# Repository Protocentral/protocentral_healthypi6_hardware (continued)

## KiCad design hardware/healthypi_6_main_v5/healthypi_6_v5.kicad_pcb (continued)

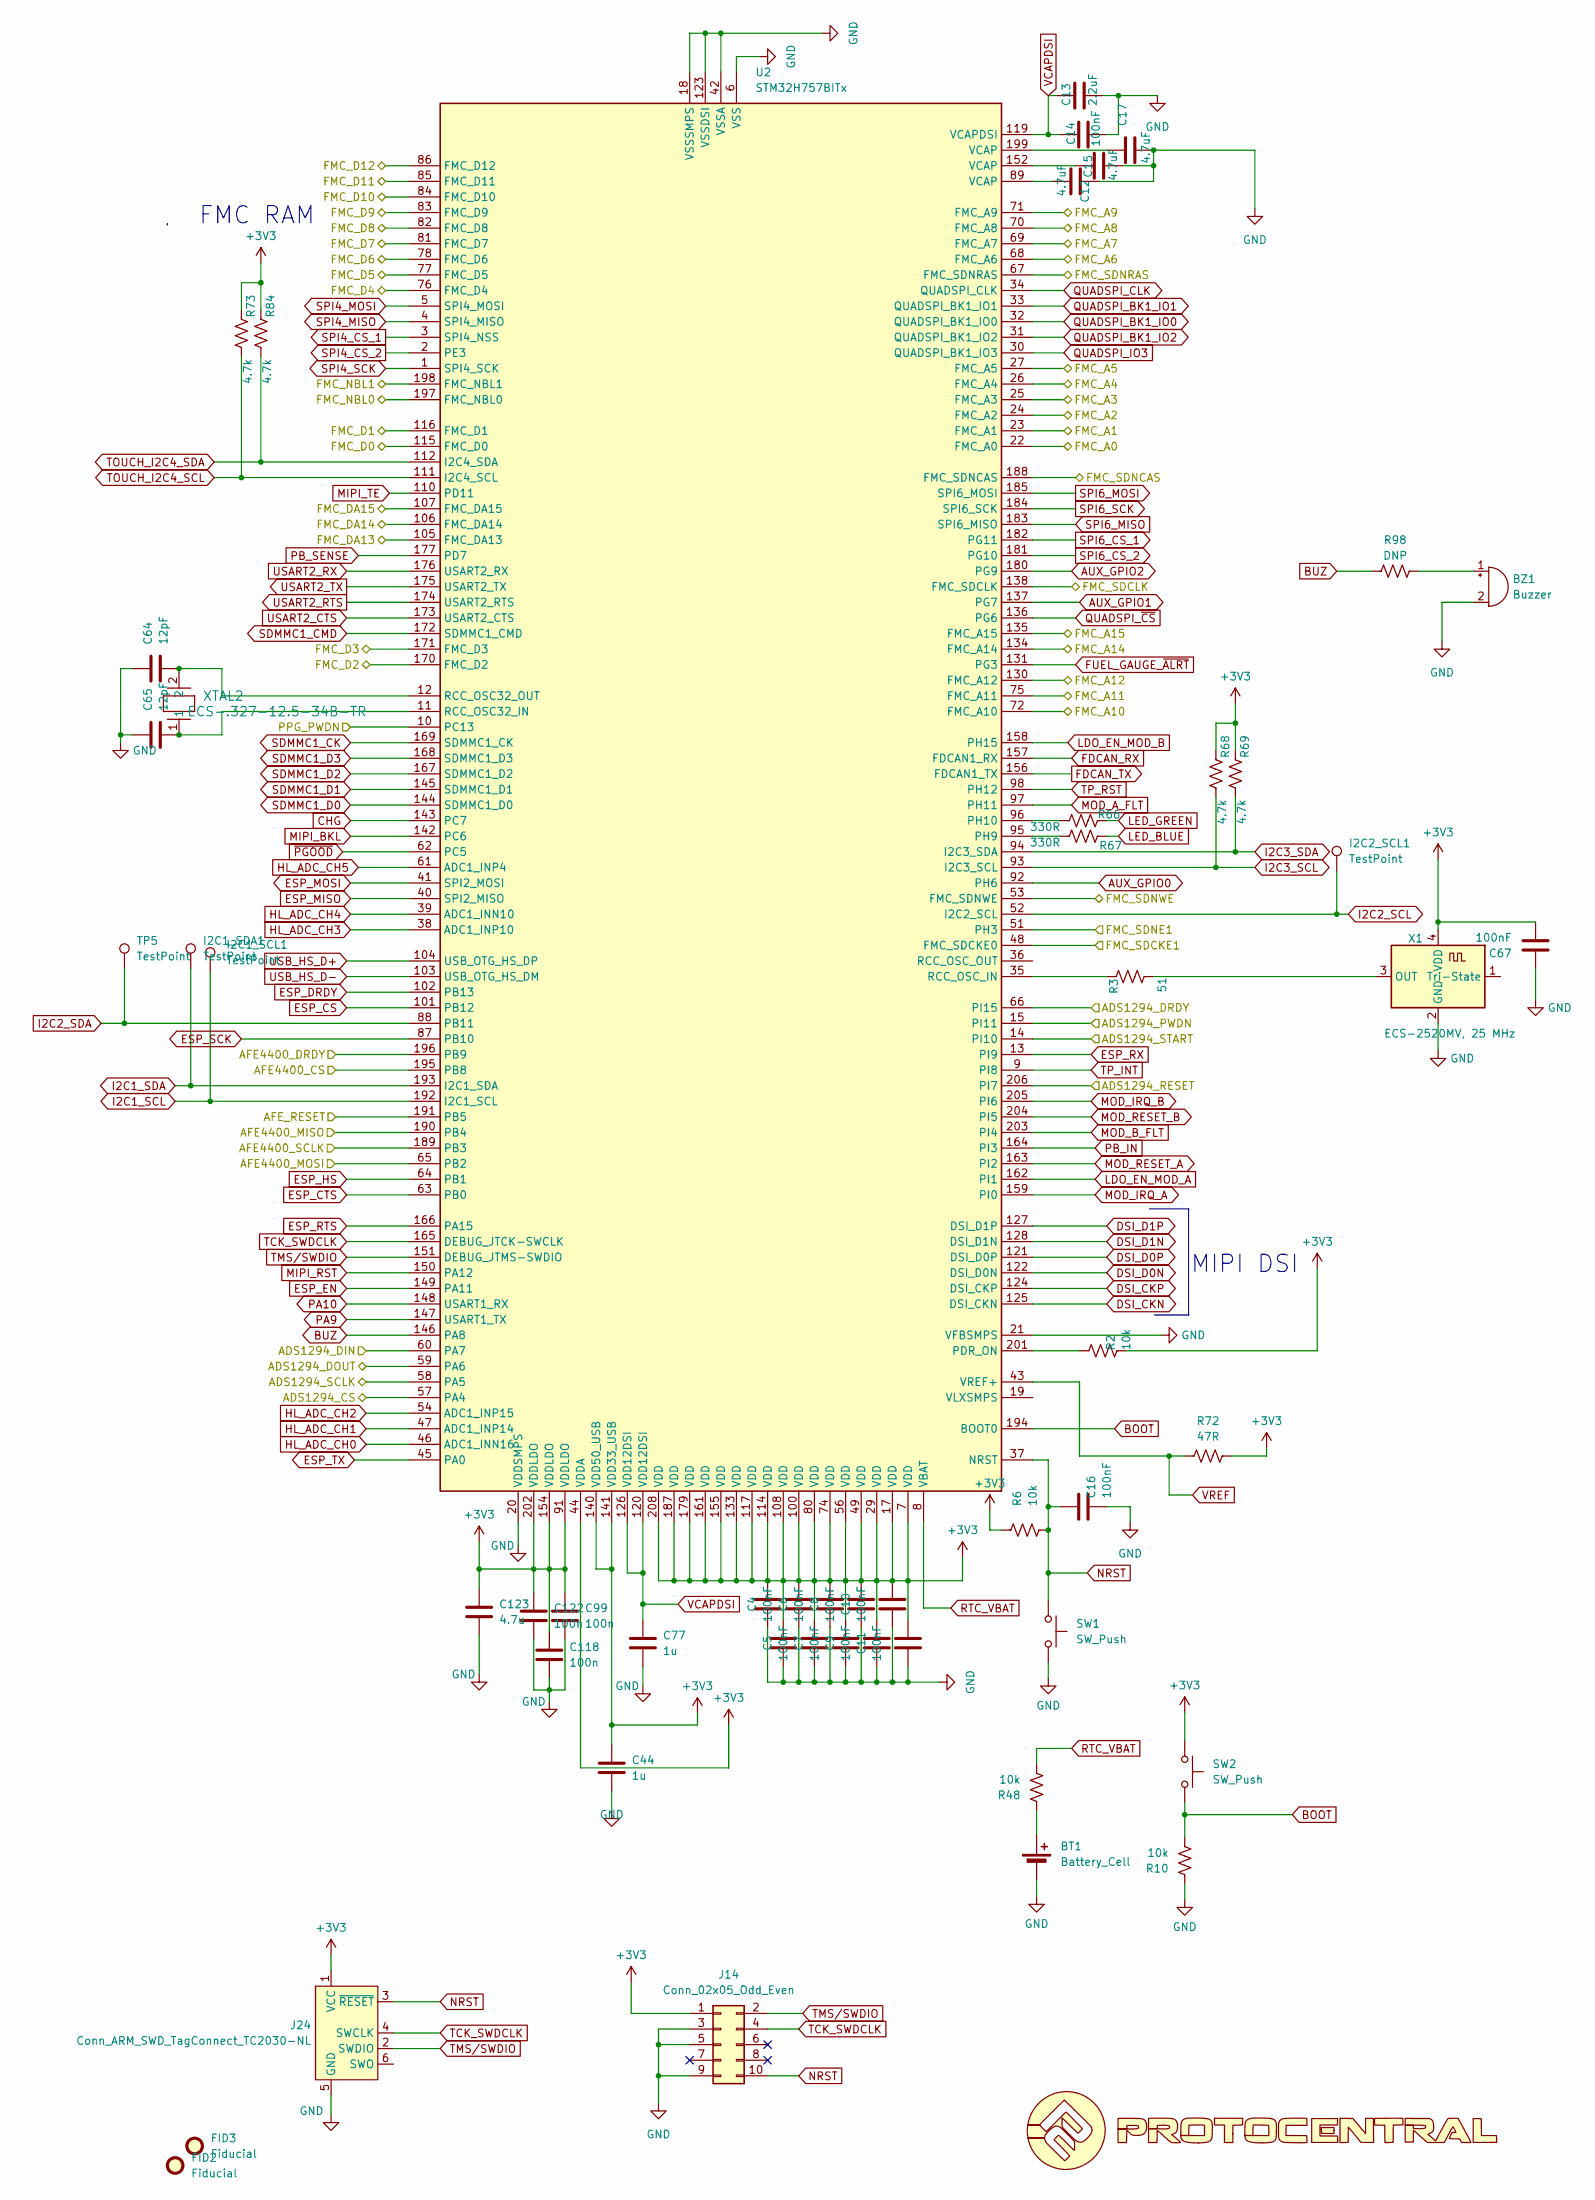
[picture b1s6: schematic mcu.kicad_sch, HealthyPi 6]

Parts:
BT1: Battery_Cell; BatteryHolder_Keystone_3001_1x12mm
BZ1: Buzzer; Buzzer_Murata_PKMCS0909E
C2, C3, C4, C5, C6, C7, C8, C9, C10, C11, C14, C16, C67: 100nF; C_0402_1005Metric
C12, C15, C17: 4.7uF; C_0402_1005Metric
C13: 2.2uF; C_0402_1005Metric
C44, C77: 1u; C_0402_1005Metric
C64, C65: 12pF; C_0402_1005Metric
C99, C118, C122: 100n; C_0402_1005Metric
C123: 4.7u; C_0402_1005Metric
FID2, FID3: Fiducial; Fiducial_1mm_Mask3mm
I2C1_SCL1, I2C1_SDA1, I2C2_SCL1: TestPoint; TestPoint_Pad_D1.0mm
J14: Conn_02x05_Odd_Even; PinHeader_2x05_P1.27mm_Vertical_SMD
J24: Conn_ARM_SWD_TagConnect_TC2030-NL; Tag-Connect_TC2030-IDC-NL_2x03_P1.27mm_Vertical
R2, R6, R10, R48: 10k; R_0402_1005Metric
R3: 51; R_0402_1005Metric
R66, R67: 330R; R_0402_1005Metric
R68, R69, R73, R84: 4.7k; R_0402_1005Metric
R72: 47R; R_0402_1005Metric
R98: DNP; R_0402_1005Metric
SW1, SW2: SW_Push; SW_Push_1P1T_NO_CK_KMR2
TP5: TestPoint; TestPoint_Pad_D1.0mm
U2: STM32H757BITx; LQFP-208_28x28mm_P0.5mm
U10: LOGO
X1: ECS-2520MV, 25 MHz; Oscillator_SMD_ECS_2520MV-xxx-xx-4Pin_2.5x2.0mm
XTAL2: ECS-.327-12.5-34B-TR; XTAL_ECS-31B_ECS

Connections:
+3V3: C2.2, C3.2, C4.2, C5.2, C6.2, C7.2, C8.2, C9.2, C10.2, C11.2, C44.1, C67.2, C99.1, C118.1, C122.1, C123.1, J14.1, J24.1 (VCC), R2.2, R6.1, R68.2, R69.2, R72.1, R73.2, R84.2, SW2.1, U2.7 (VDD), U2.17 (VDD), U2.29 (VDD), U2.44 (VDDA), U2.49 (VDD), U2.56 (VDD), U2.74 (VDD), U2.80 (VDD), U2.91 (VDDLDO), U2.100 (VDD), U2.108 (VDD), U2.114 (VDD), U2.117 (VDD), U2.133 (VDD), U2.140 (VDD50_USB), U2.141 (VDD33_USB), U2.154 (VDDLDO), U2.155 (VDD), U2.161 (VDD), U2.179 (VDD), U2.187 (VDD), U2.202 (VDDLDO), U2.208 (VDD), X1.4 (VDD); also elsewhere on the board
/ECG Frontend/ADS1294_CS: U2.57 (PA4); also elsewhere on the board
/ECG Frontend/ADS1294_DIN: U2.60 (PA7); also elsewhere on the board
/ECG Frontend/ADS1294_DOUT: U2.59 (PA6); also elsewhere on the board
/ECG Frontend/ADS1294_DRDY: U2.66 (PI15); also elsewhere on the board
/ECG Frontend/ADS1294_PWDN: U2.15 (PI11); also elsewhere on the board
/ECG Frontend/ADS1294_RESET: U2.206 (PI7); also elsewhere on the board
/ECG Frontend/ADS1294_SCLK: U2.58 (PA5); also elsewhere on the board
/ECG Frontend/ADS1294_START: U2.14 (PI10); also elsewhere on the board
/MCU/AFE4400_CS: U2.195 (PB8); also elsewhere on the board
/MCU/AFE4400_DRDY: U2.196 (PB9); also elsewhere on the board
/MCU/AFE4400_MISO: U2.190 (PB4); also elsewhere on the board
/MCU/AFE4400_MOSI: U2.65 (PB2); also elsewhere on the board
/MCU/AFE4400_SCLK: U2.189 (PB3); also elsewhere on the board
/MCU/AFE_RESET: U2.191 (PB5); also elsewhere on the board
/MCU/FMC_A0: U2.22 (FMC_A0); also elsewhere on the board
/MCU/FMC_A1: U2.23 (FMC_A1); also elsewhere on the board
/MCU/FMC_A2: U2.24 (FMC_A2); also elsewhere on the board
/MCU/FMC_A3: U2.25 (FMC_A3); also elsewhere on the board
/MCU/FMC_A4: U2.26 (FMC_A4); also elsewhere on the board
/MCU/FMC_A5: U2.27 (FMC_A5); also elsewhere on the board
/MCU/FMC_A6: U2.68 (FMC_A6); also elsewhere on the board
/MCU/FMC_A7: U2.69 (FMC_A7); also elsewhere on the board
/MCU/FMC_A8: U2.70 (FMC_A8); also elsewhere on the board
/MCU/FMC_A9: U2.71 (FMC_A9); also elsewhere on the board
/MCU/FMC_A10: U2.72 (FMC_A10); also elsewhere on the board
/MCU/FMC_A11: U2.75 (FMC_A11); also elsewhere on the board
/MCU/FMC_A12: U2.130 (FMC_A12); also elsewhere on the board
/MCU/FMC_A14: U2.134 (FMC_A14); also elsewhere on the board
/MCU/FMC_A15: U2.135 (FMC_A15); also elsewhere on the board
/MCU/FMC_D0: U2.115 (FMC_D0); also elsewhere on the board
/MCU/FMC_D1: U2.116 (FMC_D1); also elsewhere on the board
/MCU/FMC_D2: U2.170 (FMC_D2); also elsewhere on the board
/MCU/FMC_D3: U2.171 (FMC_D3); also elsewhere on the board
/MCU/FMC_D4: U2.76 (FMC_D4); also elsewhere on the board
/MCU/FMC_D5: U2.77 (FMC_D5); also elsewhere on the board
/MCU/FMC_D6: U2.78 (FMC_D6); also elsewhere on the board
/MCU/FMC_D7: U2.81 (FMC_D7); also elsewhere on the board
/MCU/FMC_D8: U2.82 (FMC_D8); also elsewhere on the board
/MCU/FMC_D9: U2.83 (FMC_D9); also elsewhere on the board
/MCU/FMC_D10: U2.84 (FMC_D10); also elsewhere on the board
/MCU/FMC_D11: U2.85 (FMC_D11); also elsewhere on the board
/MCU/FMC_D12: U2.86 (FMC_D12); also elsewhere on the board
/MCU/FMC_DA13: U2.105 (FMC_DA13); also elsewhere on the board
/MCU/FMC_DA14: U2.106 (FMC_DA14); also elsewhere on the board
/MCU/FMC_DA15: U2.107 (FMC_DA15); also elsewhere on the board
/MCU/FMC_NBL0: U2.197 (FMC_NBL0); also elsewhere on the board
/MCU/FMC_NBL1: U2.198 (FMC_NBL1); also elsewhere on the board
/MCU/FMC_SDCKE1: U2.48 (FMC_SDCKE0); also elsewhere on the board
/MCU/FMC_SDCLK: U2.138 (FMC_SDCLK); also elsewhere on the board
/MCU/FMC_SDNCAS: U2.188 (FMC_SDNCAS); also elsewhere on the board
/MCU/FMC_SDNE1: U2.51 (PH3); also elsewhere on the board
/MCU/FMC_SDNRAS: U2.67 (FMC_SDNRAS); also elsewhere on the board
/MCU/FMC_SDNWE: U2.53 (FMC_SDNWE); also elsewhere on the board
/MCU/PPG_PWDN: U2.10 (PC13); also elsewhere on the board
AUX_GPIO0: U2.92 (PH6); also elsewhere on the board
AUX_GPIO1: U2.137 (PG7); also elsewhere on the board
AUX_GPIO2: U2.180 (PG9); also elsewhere on the board
BOOT: R10.2, SW2.2, U2.194 (BOOT0)
BUZ: R98.1, U2.146 (PA8)
CHG: U2.143 (PC7); also elsewhere on the board
DSI_CKN: U2.125 (DSI_CKN); also elsewhere on the board
DSI_CKP: U2.124 (DSI_CKP); also elsewhere on the board
DSI_D0N: U2.122 (DSI_D0N); also elsewhere on the board
DSI_D0P: U2.121 (DSI_D0P); also elsewhere on the board
DSI_D1N: U2.128 (DSI_D1N); also elsewhere on the board
DSI_D1P: U2.127 (DSI_D1P); also elsewhere on the board
ESP_CS: U2.101 (PB12); also elsewhere on the board
ESP_CTS: U2.63 (PB0); also elsewhere on the board
ESP_DRDY: U2.102 (PB13); also elsewhere on the board
ESP_EN: U2.149 (PA11); also elsewhere on the board
ESP_HS: U2.64 (PB1); also elsewhere on the board
ESP_MISO: U2.40 (SPI2_MISO); also elsewhere on the board
ESP_MOSI: U2.41 (SPI2_MOSI); also elsewhere on the board
ESP_RTS: U2.166 (PA15); also elsewhere on the board
ESP_RX: U2.13 (PI9); also elsewhere on the board
ESP_SCK: U2.87 (PB10); also elsewhere on the board
ESP_TX: U2.45 (PA0); also elsewhere on the board
FDCAN_RX: U2.157 (FDCAN1_RX); also elsewhere on the board
FDCAN_TX: U2.156 (FDCAN1_TX); also elsewhere on the board
FUEL_GAUGE_~ALRT: U2.131 (PG3); also elsewhere on the board
GND: BT1.2 (-), BZ1.2 (-), C2.1, C3.1, C4.1, C5.1, C6.1, C7.1, C8.1, C9.1, C10.1, C11.1, C12.2, C13.2, C14.2, C15.2, C16.2, C17.2, C44.2, C64.1, C65.1, C67.1, C77.2, C99.2, C118.2, C122.2, C123.2, J14.3, J14.5, J14.9, J24.5 (GND), R10.1, SW1.2, U2.6 (VSS), U2.16 (VSS), U2.18 (VSSSMPS), U2.20 (VDDSMPS), U2.21 (VFBSMPS), U2.28 (VSS), U2.42 (VSSA), U2.50 (VSS), U2.55 (VSS), U2.73 (VSS), U2.79 (VSS), U2.90 (VSS), U2.99 (VSS), U2.109 (VSS), U2.113 (VSS), U2.118 (VSS), U2.123 (VSSDSI), U2.129 (VSSDSI), U2.132 (VSS), U2.139 (VSS), U2.153 (VSS), U2.160 (VSS), U2.178 (VSS), U2.186 (VSS), U2.200 (VSS), U2.207 (VSS), X1.2 (GND); also elsewhere on the board
HL_ADC_CH0: U2.46 (ADC1_INN16); also elsewhere on the board
HL_ADC_CH1: U2.47 (ADC1_INP14); also elsewhere on the board
HL_ADC_CH2: U2.54 (ADC1_INP15); also elsewhere on the board
HL_ADC_CH3: U2.38 (ADC1_INP10); also elsewhere on the board
HL_ADC_CH4: U2.39 (ADC1_INN10); also elsewhere on the board
HL_ADC_CH5: U2.61 (ADC1_INP4); also elsewhere on the board
I2C1_SCL: I2C1_SCL1.1 (1_1), U2.192 (I2C1_SCL); also elsewhere on the board
I2C1_SDA: I2C1_SDA1.1 (1_1), U2.193 (I2C1_SDA); also elsewhere on the board
I2C2_SCL: I2C2_SCL1.1 (1_1), U2.52 (I2C2_SCL); also elsewhere on the board
I2C2_SDA: TP5.1 (1_1), U2.88 (PB11); also elsewhere on the board
I2C3_SCL: R68.1, U2.93 (I2C3_SCL); also elsewhere on the board
I2C3_SDA: R69.1, U2.94 (I2C3_SDA); also elsewhere on the board
LDO_EN_MOD_A: U2.162 (PI1); also elsewhere on the board
LDO_EN_MOD_B: U2.158 (PH15); also elsewhere on the board
LED_BLUE: R67.2; also elsewhere on the board
LED_GREEN: R66.2; also elsewhere on the board
MIPI_BKL: U2.142 (PC6); also elsewhere on the board
MIPI_RST: U2.150 (PA12); also elsewhere on the board
MIPI_TE: U2.110 (PD11); also elsewhere on the board
MOD_A_FLT: U2.97 (PH11); also elsewhere on the board
MOD_B_FLT: U2.203 (PI4); also elsewhere on the board
MOD_IRQ_A: U2.159 (PI0); also elsewhere on the board
MOD_IRQ_B: U2.205 (PI6); also elsewhere on the board
MOD_RESET_A: U2.163 (PI2); also elsewhere on the board
MOD_RESET_B: U2.204 (PI5); also elsewhere on the board
NRST: C16.1, J14.10, J24.3 (~RESET), R6.2, SW1.1, U2.37 (NRST)
unnamed: BT1.1 (+), R48.1
unnamed: BZ1.1 (+), R98.2
unnamed: C12.1, U2.89 (VCAP)
unnamed: C15.1, U2.152 (VCAP)
unnamed: C17.1, U2.199 (VCAP)
unnamed: C65.2, U2.11 (RCC_OSC32_IN), XTAL2.1
unnamed: C64.2, U2.12 (RCC_OSC32_OUT), XTAL2.2
unnamed: R2.1, U2.201 (PDR_ON)
unnamed: R3.1, U2.35 (RCC_OSC_IN)
unnamed: R67.1, U2.95 (PH9)
unnamed: R66.1, U2.96 (PH10)
unnamed: R3.2, X1.3 (OUT)
PA9: U2.147 (USART1_TX); also elsewhere on the board
PA10: U2.148 (USART1_RX); also elsewhere on the board
PB_IN: U2.164 (PI3); also elsewhere on the board
PB_SENSE: U2.177 (PD7)
QUADSPI_BK1_IO0: U2.32 (QUADSPI_BK1_IO0); also elsewhere on the board
QUADSPI_BK1_IO1: U2.33 (QUADSPI_BK1_IO1); also elsewhere on the board
QUADSPI_BK1_IO2: U2.31 (QUADSPI_BK1_IO2); also elsewhere on the board
QUADSPI_CLK: U2.34 (QUADSPI_CLK); also elsewhere on the board
QUADSPI_IO3: U2.30 (QUADSPI_BK1_IO3); also elsewhere on the board
QUADSPI_~CS: U2.136 (PG6); also elsewhere on the board
RTC_VBAT: R48.2, U2.8 (VBAT)
SDMMC1_CK: U2.169 (SDMMC1_CK); also elsewhere on the board
SDMMC1_CMD: U2.172 (SDMMC1_CMD); also elsewhere on the board
SDMMC1_D0: U2.144 (SDMMC1_D0); also elsewhere on the board
SDMMC1_D1: U2.145 (SDMMC1_D1); also elsewhere on the board
SDMMC1_D2: U2.167 (SDMMC1_D2); also elsewhere on the board
SDMMC1_D3: U2.168 (SDMMC1_D3); also elsewhere on the board
SPI4_CS_1: U2.3 (SPI4_NSS); also elsewhere on the board
SPI4_CS_2: U2.2 (PE3); also elsewhere on the board
SPI4_MISO: U2.4 (SPI4_MISO); also elsewhere on the board
SPI4_MOSI: U2.5 (SPI4_MOSI); also elsewhere on the board
SPI4_SCK: U2.1 (SPI4_SCK); also elsewhere on the board
SPI6_CS_1: U2.182 (PG11); also elsewhere on the board
SPI6_CS_2: U2.181 (PG10); also elsewhere on the board
SPI6_MISO: U2.183 (SPI6_MISO); also elsewhere on the board
SPI6_MOSI: U2.185 (SPI6_MOSI); also elsewhere on the board
SPI6_SCK: U2.184 (SPI6_SCK); also elsewhere on the board
TCK_SWDCLK: J14.4, J24.4 (SWCLK), U2.165 (DEBUG_JTCK-SWCLK)
TMS/SWDIO: J14.2, J24.2 (SWDIO), U2.151 (DEBUG_JTMS-SWDIO)
TOUCH_I2C4_SCL: R73.1, U2.111 (I2C4_SCL); also elsewhere on the board
TOUCH_I2C4_SDA: R84.1, U2.112 (I2C4_SDA); also elsewhere on the board
TP_INT: U2.9 (PI8); also elsewhere on the board
TP_RST: U2.98 (PH12); also elsewhere on the board
USART2_CTS: U2.173 (USART2_CTS); also elsewhere on the board
USART2_RTS: U2.174 (USART2_RTS); also elsewhere on the board
USART2_RX: U2.176 (USART2_RX); also elsewhere on the board
USART2_TX: U2.175 (USART2_TX); also elsewhere on the board
USB_HS_D+: U2.104 (USB_OTG_HS_DP); also elsewhere on the board
USB_HS_D-: U2.103 (USB_OTG_HS_DM); also elsewhere on the board
VCAPDSI: C13.1, C14.1, C77.1, U2.119 (VCAPDSI), U2.120 (VDD12DSI), U2.126 (VDD12DSI)
VREF: R72.2, U2.43 (VREF+)
~PGOOD: U2.62 (PC5); also elsewhere on the board

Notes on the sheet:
FMC RAM
MIPI DSI

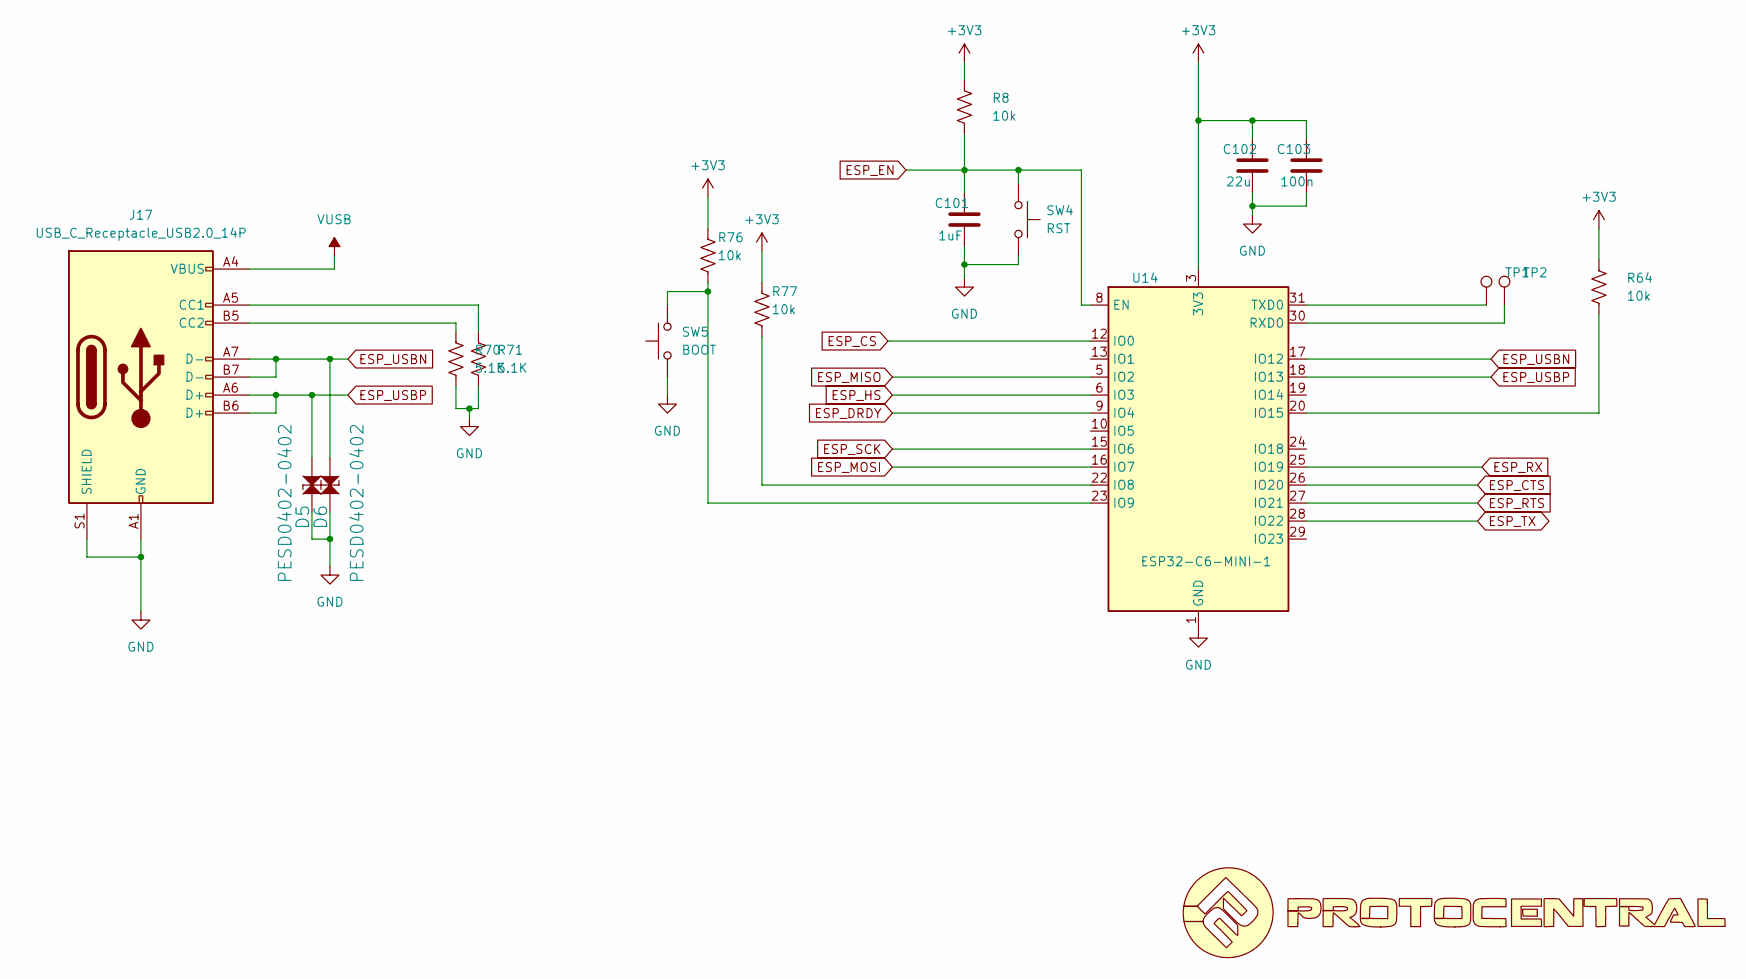
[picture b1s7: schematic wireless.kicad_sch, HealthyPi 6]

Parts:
C101: 1uF; C_0402_1005Metric
C102: 22u; C_0805_2012Metric
C103: 100n; C_0402_1005Metric
D5, D6: PESD0402-0402; D_SOD-882D
J17: USB_C_Receptacle_USB2.0_14P; USB_C_Receptacle_GCT_USB4105-xx-A_16P_TopMnt_Horizontal
R8, R64, R76, R77: 10k; R_0402_1005Metric
R70, R71: 5.1K; R_0402_1005Metric
SW4: RST; SW_Push_1P1T_NO_CK_KMR2
SW5: BOOT; SW_Push_1P1T_NO_CK_KMR2
TP1, TP2: TestPoint; TestPoint_Pad_1.0x1.0mm
U14: ESP32-C6-MINI-1
U20: LOGO

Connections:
+3V3: C102.2, C103.2, R8.1, R64.1, R76.1, R77.1, U14.3 (3V3); also elsewhere on the board
ESP_CS: U14.12 (IO0); also elsewhere on the board
ESP_CTS: U14.26 (IO20); also elsewhere on the board
ESP_DRDY: U14.9 (IO4); also elsewhere on the board
ESP_EN: C101.2, R8.2, SW4.1, U14.8 (EN); also elsewhere on the board
ESP_HS: U14.6 (IO3); also elsewhere on the board
ESP_MISO: U14.5 (IO2); also elsewhere on the board
ESP_MOSI: U14.16 (IO7); also elsewhere on the board
ESP_RTS: U14.27 (IO21); also elsewhere on the board
ESP_RX: U14.25 (IO19); also elsewhere on the board
ESP_SCK: U14.15 (IO6); also elsewhere on the board
ESP_TX: U14.28 (IO22); also elsewhere on the board
ESP_USBN: D6.2, J17.A7 (D-), J17.B7 (D-), U14.17 (IO12)
ESP_USBP: D5.2, J17.A6 (D+), J17.B6 (D+), U14.18 (IO13)
GND: C101.1, C102.1, C103.1, D5.1, D6.1, J17.A1 (GND), J17.A12 (GND), J17.B1 (GND), J17.B12 (GND), J17.S1 (SHIELD), R70.1, R71.2, SW4.2, SW5.1, U14.1 (GND), U14.2 (GND), U14.11 (GND), U14.14 (GND), U14.36 (GND), U14.37 (GND), U14.38 (GND), U14.39 (GND), U14.40 (GND), U14.41 (GND), U14.42 (GND), U14.43 (GND), U14.44 (GND), U14.45 (GND), U14.46 (GND), U14.47 (GND), U14.48 (GND), U14.49 (GND), U14.50 (GND), U14.51 (GND), U14.52 (GND), U14.53 (GND); also elsewhere on the board
unnamed: J17.A5 (CC1), R71.1
unnamed: J17.B5 (CC2), R70.2
unnamed: R77.2, U14.22 (IO8)
unnamed: R76.2, SW5.2, U14.23 (IO9)
unnamed: R64.2, U14.20 (IO15)
unnamed: TP2.1 (1_1), U14.30 (RXD0)
unnamed: TP1.1 (1_1), U14.31 (TXD0)
VUSB: J17.A4 (VBUS), J17.A9 (VBUS), J17.B4 (VBUS), J17.B9 (VBUS); also elsewhere on the board

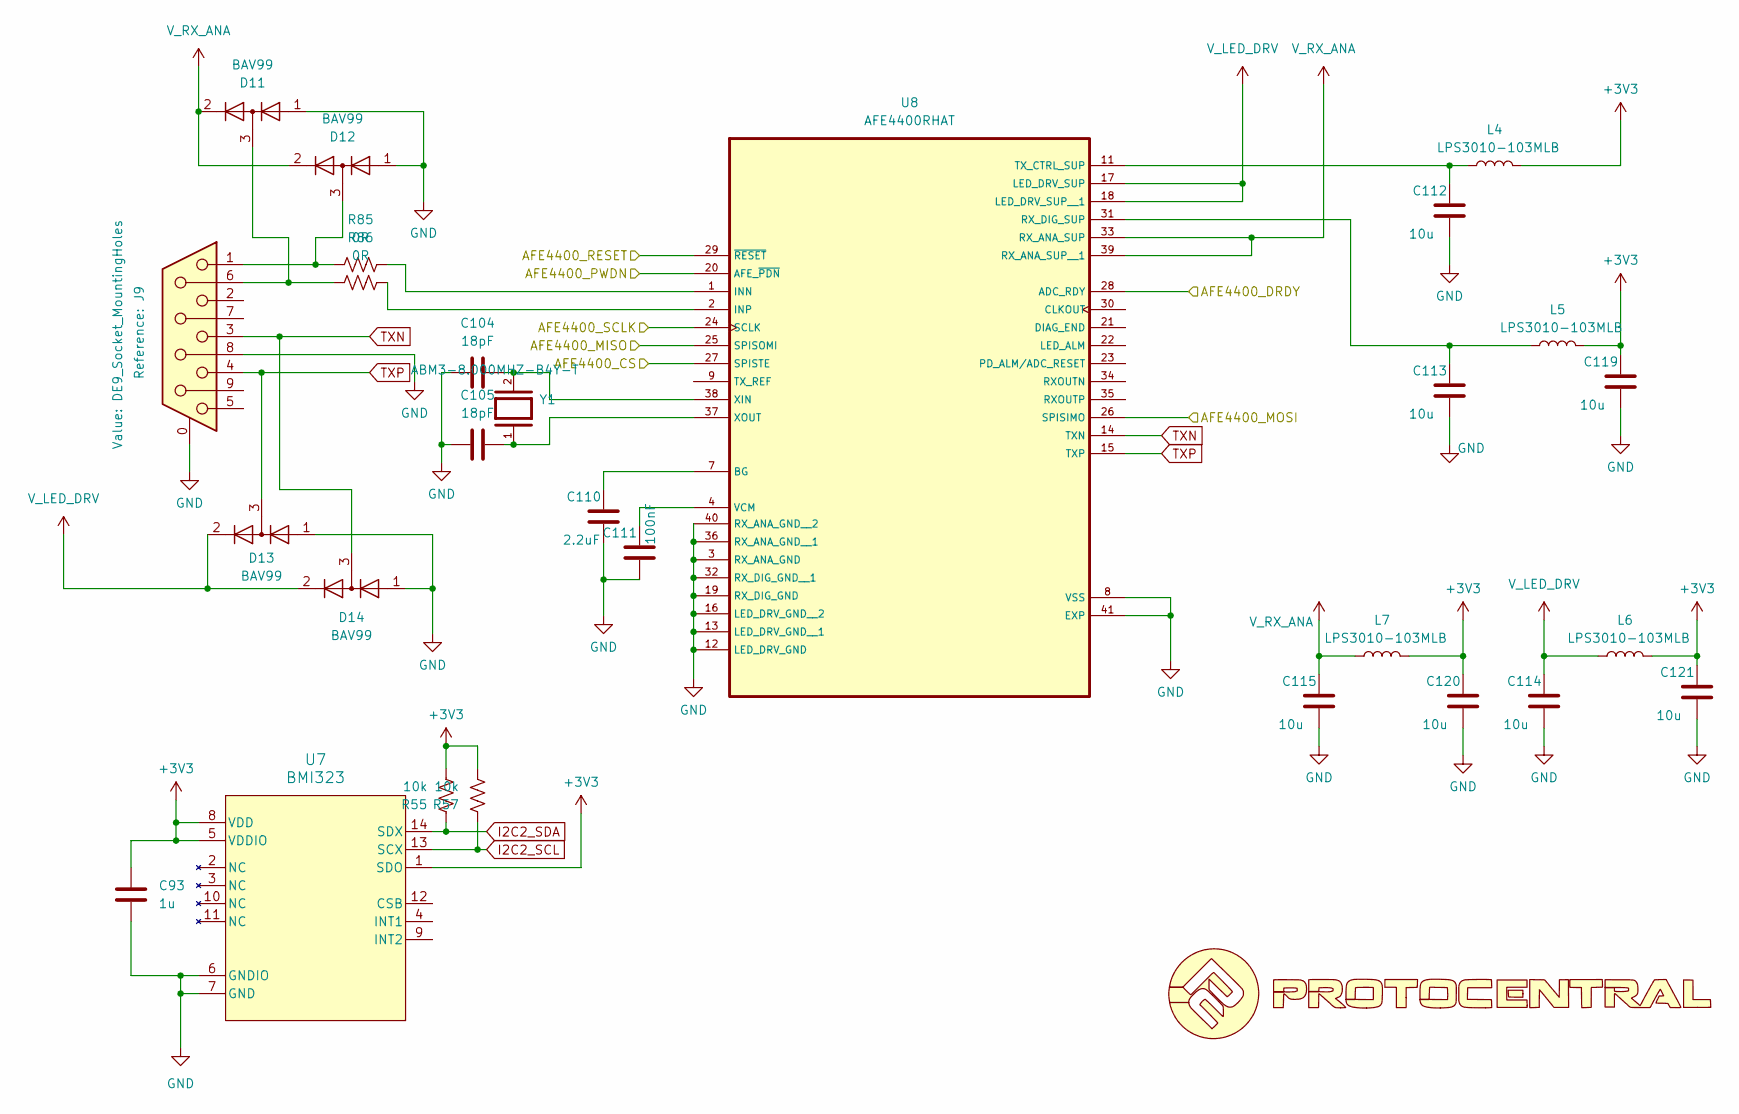
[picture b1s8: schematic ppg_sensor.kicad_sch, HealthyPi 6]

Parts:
C93: 1u; C_0402_1005Metric
C104, C105: 18pF; C_0402_1005Metric
C110: 2.2uF; C_0402_1005Metric
C111: 100nF; C_0402_1005Metric
C112, C113, C114, C115, C119, C120, C121: 10u; C_0805_2012Metric
D11, D12, D13, D14: BAV99; SOT-23
J9: DE9_Socket_MountingHoles; DSUB-9_Pins_Horizontal_P2.77x2.84mm_EdgePinOffset7.70mm_Hou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
L4, L5, L6, L7: LPS3010-103MLB; L_Coilcraft_LPS3010
R55, R57: 10k; R_0402_1005Metric
R85, R86: 0R; R_0402_1005Metric
U7: BMI323; BMI323_BOS
U8: AFE4400RHAT; Texas_RHA_VQFN-40-1EP_6x6mm_P0.5mm_EP4.6x4.6mm_ThermalVias
U19: LOGO
Y1: ABM3-8.000MHZ-B4Y-T; XTAL_ABM3-8.000MHZ-B4Y-T; PARTREV 4/25/2022

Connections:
+3V3: C93.2, C119.1, C120.1, C121.1, L4.2, L5.2, L6.2, L7.2, R55.2, R57.2, U7.1 (SDO), U7.5 (VDDIO), U7.8 (VDD); also elsewhere on the board
/MCU/AFE4400_CS: U8.27 (SPISTE); also elsewhere on the board
/MCU/AFE4400_DRDY: U8.28 (ADC_RDY); also elsewhere on the board
/MCU/AFE4400_MISO: U8.25 (SPISOMI); also elsewhere on the board
/MCU/AFE4400_MOSI: U8.26 (SPISIMO); also elsewhere on the board
/MCU/AFE4400_SCLK: U8.24 (SCLK); also elsewhere on the board
/MCU/AFE_RESET: U8.29 (~RESET); also elsewhere on the board
/MCU/PPG_PWDN: U8.20 (AFE_~PDN); also elsewhere on the board
GND: C93.1, C104.2, C105.2, C110.2, C111.2, C112.2, C113.2, C114.2, C115.2, C119.2, C120.2, C121.2, D11.1 (K), D12.1 (K), D13.1 (K), D14.1 (K), J9.0 (PAD), J9.8, U7.6 (GNDIO), U7.7 (GND), U8.3 (RX_ANA_GND), U8.8 (VSS), U8.12 (LED_DRV_GND), U8.13 (LED_DRV_GND__1), U8.16 (LED_DRV_GND__2), U8.19 (RX_DIG_GND), U8.32 (RX_DIG_GND__1), U8.36 (RX_ANA_GND__1), U8.40 (RX_ANA_GND__2), U8.41 (EXP); also elsewhere on the board
I2C2_SCL: R57.1, U7.13 (SCX); also elsewhere on the board
I2C2_SDA: R55.1, U7.14 (SDX); also elsewhere on the board
unnamed: D11.3 (K), J9.6, R86.1
unnamed: D12.3 (K), J9.1, R85.1
unnamed: C110.1, U8.7 (BG)
unnamed: R85.2, U8.1 (INN)
unnamed: R86.2, U8.2 (INP)
unnamed: C113.1, L5.1, U8.31 (RX_DIG_SUP)
unnamed: C112.1, L4.1, U8.11 (TX_CTRL_SUP)
unnamed: C111.1, U8.4 (VCM)
unnamed: C104.1, U8.38 (XIN), Y1.2
unnamed: C105.1, U8.37 (XOUT), Y1.1
TXN: D14.3 (K), J9.3, U8.14 (TXN)
TXP: D13.3 (K), J9.4, U8.15 (TXP)
V_LED_DRV: C114.1, D13.2 (A), D14.2 (A), L6.1, U8.17 (LED_DRV_SUP), U8.18 (LED_DRV_SUP__1)
V_RX_ANA: C115.1, D11.2 (A), D12.2 (A), L7.1, U8.33 (RX_ANA_SUP), U8.39 (RX_ANA_SUP__1)

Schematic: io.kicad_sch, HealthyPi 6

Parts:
C66, C79: 1u; C_0805_2012Metric
C68: 10uF /16V; C_0805_2012Metric
C69: 22u; C_0805_2012Metric
C70: 100nF; C_0402_1005Metric
C71: 100nF / 16V; C_0402_1005Metric
C74: 4.7u; C_0805_2012Metric
C78, C89: 100n; C_0805_2012Metric
CR1: ESDA25W; SOT-323_SC-70
CR2: ESDA25P35-1U1M; ST_QFN-2L_1.6x1.0mm
D1, D2: PESD0402-0402; D_SOD-882D
D3: SMAJ6.0CA; D_SMA
J3: USB_C_Receptacle_USB2.0_14P; USB_C_Receptacle_GCT_USB4105-xx-A_16P_TopMnt_Horizontal
PS1: THM_10-0511; CONV_THM_10-0511; PARTREV May 17, 2024
R7, R9: 5.1k; R_0402_1005Metric
U5: ISOUSB111DWR; SOIC16_DW_TEX
U17: LOGO

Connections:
+3V3: C79.2, C89.2, U5.12 (PIN), U5.14 (V3P3V2), U5.16 (VBUS2); also elsewhere on the board
CC1: CR1.2, J3.A5 (CC1), R9.2
CC2: CR1.1, J3.B5 (CC2), R7.2
GND: C69.1, C70.1, C74.1, C79.1, C89.1, PS1.12 (-VOUT), U5.9 (GND2), U5.15 (GND2); also elsewhere on the board
unnamed: C68.2, C71.2, D3.1 (A1), PS1.1 (+VIN(VCC))
unnamed: C78.2, U5.3 (V3P3V1)
USB_D+: D1.2, J3.A6 (D+), J3.B6 (D+), U5.7 (UD+)
USB_D-: D2.2, J3.A7 (D-), J3.B7 (D-), U5.6 (UD-)
USB_HS_D+: U5.10 (DD+); also elsewhere on the board
USB_HS_D-: U5.11 (DD-); also elsewhere on the board
VBUS: C66.2, CR2.1, D3.2 (A2), J3.A4 (VBUS), J3.A9 (VBUS), J3.B4 (VBUS), J3.B9 (VBUS), U5.1 (VBUS1)
VSS: C66.1, C68.1, C71.1, C78.1, CR1.3, CR2.2, D1.1, D2.1, J3.A1 (GND), J3.A12 (GND), J3.B1 (GND), J3.B12 (GND), J3.S1 (SHIELD), PS1.23 (-VIN(GND)), PS1.24 (-VIN(GND)__1), R7.1, R9.1, U5.2 (GND1), U5.8 (GND1)
VUSB: C69.2, C70.2, C74.2, PS1.13 (+VOUT); also elsewhere on the board

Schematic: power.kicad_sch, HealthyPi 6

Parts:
3V3: TestPoint; TestPoint_Pad_D1.0mm
C50: 100nF; C_0402_1005Metric; Voltage 25V; Tolerance 20%
C57: 1u; C_0805_2012Metric
C58, C73, C95: 4.7u; C_0805_2012Metric
C94: 220u, 1206; C_1206_3216Metric
C116: 22u; C_0805_2012Metric
C117: DNP; C_0402_1005Metric
J5: JST_2mm_LiPo; JST_PH_S2B-PH-SM4-TB_1x02-1MP_P2.00mm_Horizontal
L10: DFE252012F-1R0M, 1uH; L_1008_2520Metric
R11: 1.1k; R_0402_1005Metric
R12: 590; R_0402_1005Metric
R13: R_US; R_0402_1005Metric
R14, R35: 10k; R_0402_1005Metric
R16: 1.5k; R_0402_1005Metric
R74: 453k; R_0402_1005Metric
R75: 100k; R_0402_1005Metric
SW3: SW_SPDT; SW_SPDT_CK_JS102011SAQN
U9: BQ24074RGT; VQFN-16-1EP_3x3mm_P0.5mm_EP1.6x1.6mm
U11: TPS62A02APDDC; SOT-23-6
U12: MAX17048; SON50P200X200X80-9N
U18: LOGO
VBAT1: TestPoint; TestPoint_Pad_D1.0mm
VSYS1: TestPoint; TestPoint_Pad_D1.0mm

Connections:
+3V3: 3V3.1 (1_1), C116.1, C117.2, L10.2, R35.1, R74.2; also elsewhere on the board
CHG: R16.1, U9.9 (~CHG); also elsewhere on the board
FUEL_GAUGE_~ALRT: R35.2, U12.5 (~ALRT); also elsewhere on the board
GND: C50.2, C57.2, C58.2, C73.2, C94.2, C95.2, C116.2, J5.2, J5.MP (MountPin), R11.1, R12.1, R13.1, R14.2, R75.1, SW3.3 (C), U9.4 (~CE), U9.6 (EN1), U9.8 (VSS), U9.14 (TMR), U9.17 (VSS), U11.2 (GND), U12.1 (CTG), U12.4 (GND), U12.6 (QSTRT), U12.9 (GND); also elsewhere on the board
I2C2_SCL: U12.7 (SCL); also elsewhere on the board
I2C2_SDA: U12.8 (SDA); also elsewhere on the board
LED_CHG: R16.2; also elsewhere on the board
unnamed: SW3.2 (B), U11.1 (EN)
unnamed: R11.2, U9.12 (ILIM)
unnamed: R12.2, U9.16 (ISET)
unnamed: R13.2, U9.15 (ITERM)
unnamed: R14.1, U9.1 (TS)
unnamed: C117.1, R74.1, R75.2, U11.6 (FB)
unnamed: L10.1, U11.3 (SW)
VBATT: C50.1, C73.1, J5.1, U9.2 (BAT), U9.3 (BAT), U12.2 (CELL), U12.3 (VDD), VBAT1.1 (1_1)
VSYS: C58.1, C94.1, C95.1, SW3.1 (A), U9.10 (OUT), U9.11 (OUT), U11.4 (VIN), VSYS1.1 (1_1); also elsewhere on the board
VUSB: C57.1, U9.5 (EN2), U9.13 (IN); also elsewhere on the board
~PGOOD: U9.7 (~PGOOD); also elsewhere on the board

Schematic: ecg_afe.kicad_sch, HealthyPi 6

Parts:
C19, C22: 2.2n; C_0402_1005Metric
C20, C30: 470p; C_0402_1005Metric
C21, C31, C37, C80, C84, C85, C86, C87: 100nF; C_0402_1005Metric
C23: 4.7uF; C_0402_1005Metric
C32, C33, C34, C35, C88, C90: 47p; C_0402_1005Metric
C36, C39, C40, C41, C81: 1u; C_0402_1005Metric
C38: 22u; C_0805_2012Metric
C42: 1.5n; C_0402_1005Metric
C43: 47pF; C_0402_1005Metric
C82, C83, C91, C92: 1uF; C_0402_1005Metric
C151: 10uF; C_0805_2012Metric
IC1: ADS1294RIZXGR; BGA64C80P8X8_800X800X145; Manufacturer_Part_Number ADS1294RIZXGR; Mouser Part Number 595-ADS1294RIZXGR
J6: Conn_01x06_Socket; PinHeader_1x06_P2.54mm_Vertical
L8: BLM18PG600SN1; LED_0603_1608Metric
R4, R5: 40.2k; R_0402_1005Metric
R19, R20, R21, R22: 10M; R_0402_1005Metric
R23, R24, R25, R26: 22k; R_0402_1005Metric
R27: 1M; R_0402_1005Metric
R28: 22K; R_0402_1005Metric
R34, R38: 221.k; R_0402_1005Metric
R49: 4.7k; R_0402_1005Metric
R56: 0R; R_0402_1005Metric
U15: LOGO
U21: TPD6E05U06RVZ; Texas_R-PUSON-N14

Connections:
+3V3: L8.1, R20.2, R21.2; also elsewhere on the board
/ECG Frontend/ADS1294_CS: IC1.F7 (~CS); also elsewhere on the board
/ECG Frontend/ADS1294_DIN: IC1.H8 (DIN); also elsewhere on the board
/ECG Frontend/ADS1294_DOUT: IC1.E8 (DOUT); also elsewhere on the board
/ECG Frontend/ADS1294_DRDY: IC1.D6 (~DRDY); also elsewhere on the board
/ECG Frontend/ADS1294_PWDN: IC1.G5 (~PWDN); also elsewhere on the board
/ECG Frontend/ADS1294_RESET: IC1.G6 (~RESET); also elsewhere on the board
/ECG Frontend/ADS1294_SCLK: IC1.F8 (SCLK); also elsewhere on the board
/ECG Frontend/ADS1294_START: IC1.G7 (START); also elsewhere on the board
ECG_IN3_N: C32.1, C90.1, J6.2, R26.2, R34.2, U21.9 (D3+)
ECG_IN3_P: C33.1, J6.3, R25.2, U21.11 (D2-)
ECG_IN4_N: C34.1, IC1.D3 (WCT), R24.2
ECG_IN4_P: C35.1, J6.4, R23.2, U21.12 (D2+)
ECG_RA: C88.1, J6.1, R38.2, U21.8 (D3-)
ECG_RLD: C43.2, J6.6, R28.1, R49.2, U21.14 (D1+)
GND: C23.2, C32.2, C33.2, C34.2, C35.2, C36.1, C37.1, C38.1, C39.1, C40.1, C41.1, C43.1, C80.1, C81.1, C82.1, C83.1, C84.1, C85.1, C86.1, C87.1, C88.2, C90.2, C91.1, C92.1, C151.1, IC1.A5 (AVSS_1), IC1.A8 (AVSS1), IC1.B5 (AVSS_2), IC1.C5 (AVSS_3), IC1.C7 (DGND_1), IC1.D4 (AVSS_4), IC1.D5 (AVSS_5), IC1.D7 (DGND_2), IC1.E4 (RESV1), IC1.H4 (VREFN), IC1.H7 (DGND_3), R19.2, R22.2, U21.5 (GND), U21.10 (GND); also elsewhere on the board
unnamed: C19.1, R4.2
unnamed: C19.2, C30.2, C31.2
unnamed: C20.1, C21.2, C22.2
unnamed: C22.1, R5.2
unnamed: C20.2, IC1.H2 (IN1N), R21.1, R22.1
unnamed: C30.1, IC1.H1 (IN1P), R19.1, R20.1
unnamed: C21.1, IC1.G2 (IN2N), R38.1
unnamed: C31.1, IC1.G1 (IN2P), R34.1
unnamed: IC1.F2 (IN3N), R26.1
unnamed: IC1.F1 (IN3P), R25.1
unnamed: IC1.E2 (IN4N), R24.1
unnamed: IC1.E1 (IN4P), R23.1
unnamed: IC1.G4 (RESP_MODP), R4.1
unnamed: IC1.F4 (RESP__MODN), R5.1
unnamed: IC1.A3 (RLDIN), R56.2
unnamed: C42.1, IC1.C3 (RLDINV), R27.1
unnamed: C42.2, IC1.B3 (RLDOUT), R27.2, R28.2, R56.1
unnamed: C38.2, IC1.H5 (VCAP1)
unnamed: C39.2, IC1.H6 (VCAP2)
unnamed: C36.2, C40.2, IC1.B7 (VCAP3)
unnamed: C41.2, IC1.G3 (VCAP4)
unnamed: C37.2, C151.2, IC1.H3 (VREFP)
SHIELD: J6.5, R49.1, U21.13 (D1-)
VDD_ECG_AFE: C23.1, C80.2, C81.2, C82.2, C83.2, C84.2, C85.2, C86.2, C87.2, C91.2, C92.2, IC1.A1 (IN8P), IC1.A2 (IN8N), IC1.A4 (AVDD_1), IC1.A6 (AVDD_2), IC1.A7 (AVDD1), IC1.B1 (IN7P), IC1.B2 (IN7N), IC1.B4 (AVDD_3), IC1.B6 (AVDD_4), IC1.B8 (CLKSEL), IC1.C1 (IN6P), IC1.C2 (IN6N), IC1.C6 (AVDD_5), IC1.C8 (DVDD_1), IC1.D1 (IN5P), IC1.D2 (IN5N), IC1.D8 (DVDD_2), L8.2

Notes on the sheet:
BLM18PG600SN1
